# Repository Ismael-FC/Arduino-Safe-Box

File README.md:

# Arduino-Safe-Box

O projeto consiste num simples mecanismo de trancar e destrancar uma caixa, mediante a apresentação de password/PIN ou não. 

Materiais utilizados:
- Arduino MEGA;
- Breadboard;
- Sensor ultrassónico;
- Servomotor SG90;
- 2 LEDs;
- 3 Resistências de 220 Ohm;
- 1 Buzzer (passivo ou ativo);
- Display LED 16x2 I2C;
- Matriz de Botões 4x4;
- Sensor de vibração.

Modo de funcionamento:
Com PIN indefinido, a porta estará aberta e o utilizador terá a possibilidade de definir um PIN através da matriz de botões 
ao pressionar o botão A. Nesse caso, a máquina irá passar para um estado onde estará a guardar a password (limitada a 10 caracteres).
Se o utilizador se enganar, pode pressionar C; quando finalizar, deve pressionar #. O utilizador pode trancar a caixa com um botão externo. 

Definido um PIN, o sistema entra em stand-by. O sensor procura indivíduos próximos a cada 100 ms. Em caso de deteção, o display
irá saudar o indivíduo e apresentar as opções B para login e S para reset da password.

Se nas 3 tentativas de log-in o utilizador errar o PIN, o sistema entra em modo LOCK pelo que faz soar um alarme e impede novas tentativas de
log-in ou reset. Em caso de entrada forçada na caixa, um sensor de vibração será ativado o que também leva o sistema o modo LOCK.

Caso o utilizador acerte o PIN, o servmotor roda de modo a destrancar a caixa. O utilizador pode trancar a caixa com um botão externo. 
O sistema volta ao estado de stand-by.

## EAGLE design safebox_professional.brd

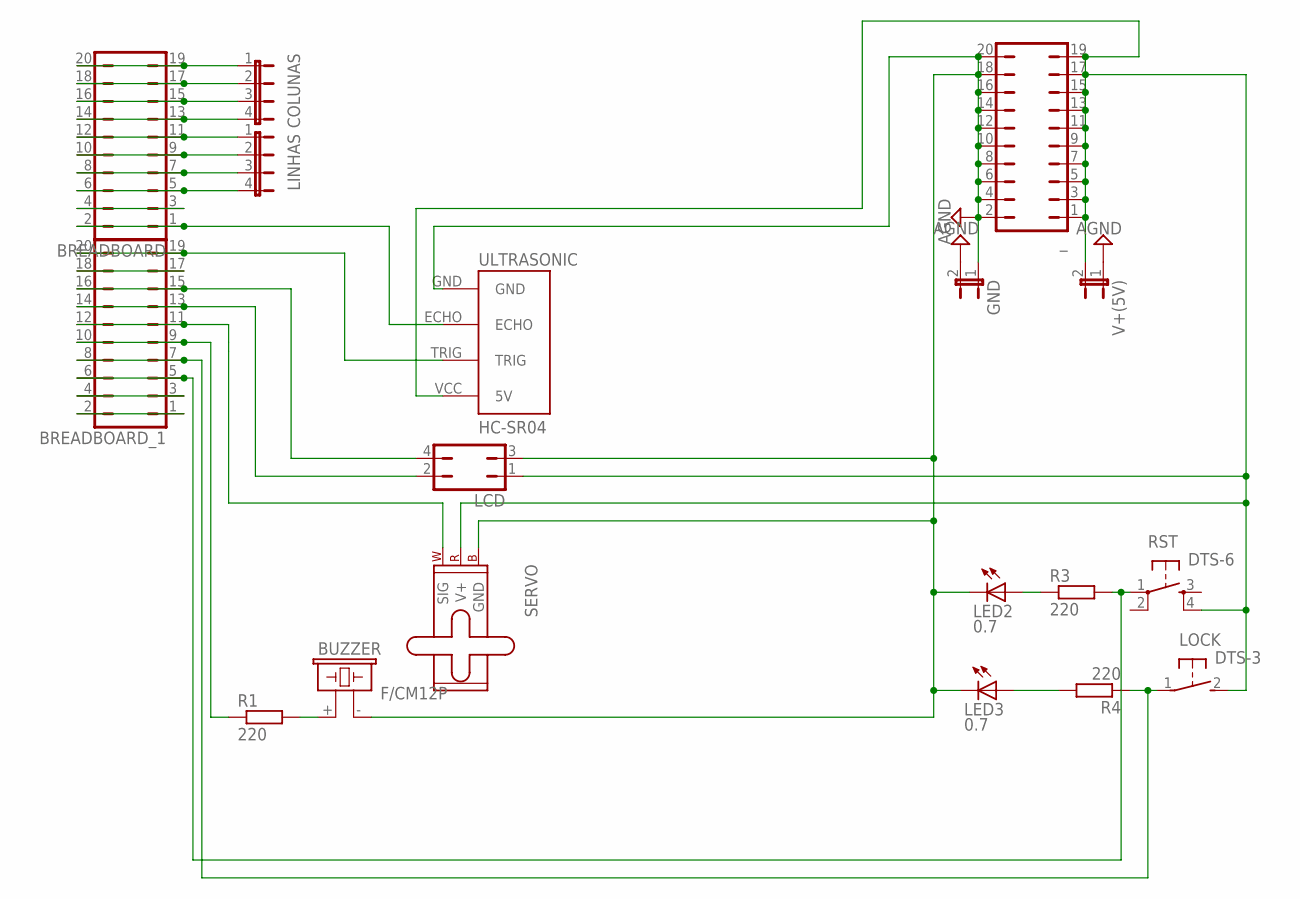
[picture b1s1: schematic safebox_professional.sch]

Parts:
BREADBOARD: JP10Q
BREADBOARD_1: JP10Q
BUZZER: F/CM12P
COLUNAS: JP4E; JP4
GND: JP1E; JP1
LCD: JP2Q
LED2, LED3: 0.7; LED5MM
LINHAS: JP4E; JP4
LOCK: DTS-3
M2: SERVO; 1X03
R1, R3, R4: 220; 0207/12
RST: DTS-6
ULTRASONIC: HC-SR04; HC-SR04_FOOTPRINT
V+(5V): JP1E; JP1
_: JP10Q

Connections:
AGND: BUZZER.- (2), GND.1, GND.2, LCD.3, LED2.K (C), LED3.K (C), M2.3 (GND), ULTRASONIC.GND, V+(5V).1, _.2, _.4, _.6, _.8, _.10, _.12, _.14, _.16, _.18, _.20
unnamed: BREADBOARD_1.5, BREADBOARD_1.6, R3.2, RST.1
unnamed: BREADBOARD_1.1, BREADBOARD_1.2
unnamed: BREADBOARD.19, BREADBOARD.20, COLUNAS.1
unnamed: BREADBOARD.17, BREADBOARD.18, COLUNAS.2
unnamed: BREADBOARD.15, BREADBOARD.16, COLUNAS.3
unnamed: BREADBOARD.13, BREADBOARD.14, COLUNAS.4
unnamed: BREADBOARD.11, BREADBOARD.12, LINHAS.1
unnamed: BREADBOARD.9, BREADBOARD.10, LINHAS.2
unnamed: BREADBOARD.7, BREADBOARD.8, LINHAS.3
unnamed: BREADBOARD.5, BREADBOARD.6, LINHAS.4
unnamed: LED2.A, R3.1
unnamed: BUZZER.+ (1), R1.2
unnamed: BREADBOARD.1, BREADBOARD.2, ULTRASONIC.ECHO
unnamed: BREADBOARD_1.15, BREADBOARD_1.16, LCD.4
unnamed: BREADBOARD_1.13, BREADBOARD_1.14, LCD.2
unnamed: BREADBOARD_1.17, BREADBOARD_1.18
unnamed: BREADBOARD_1.9, BREADBOARD_1.10, R1.1
unnamed: BREADBOARD_1.7, BREADBOARD_1.8, LOCK.1, R4.1
unnamed: BREADBOARD_1.11, BREADBOARD_1.12, M2.1 (SIG)
unnamed: BREADBOARD.3, BREADBOARD.4
unnamed: BREADBOARD_1.19, BREADBOARD_1.20, ULTRASONIC.TRIG
unnamed: BREADBOARD_1.3, BREADBOARD_1.4
unnamed: LED3.A, R4.2
unnamed: LCD.1, LOCK.2, M2.2 (V+), RST.4, ULTRASONIC.VCC (5V), V+(5V).2, _.1, _.3, _.5, _.7, _.9, _.11, _.13, _.15, _.17, _.19

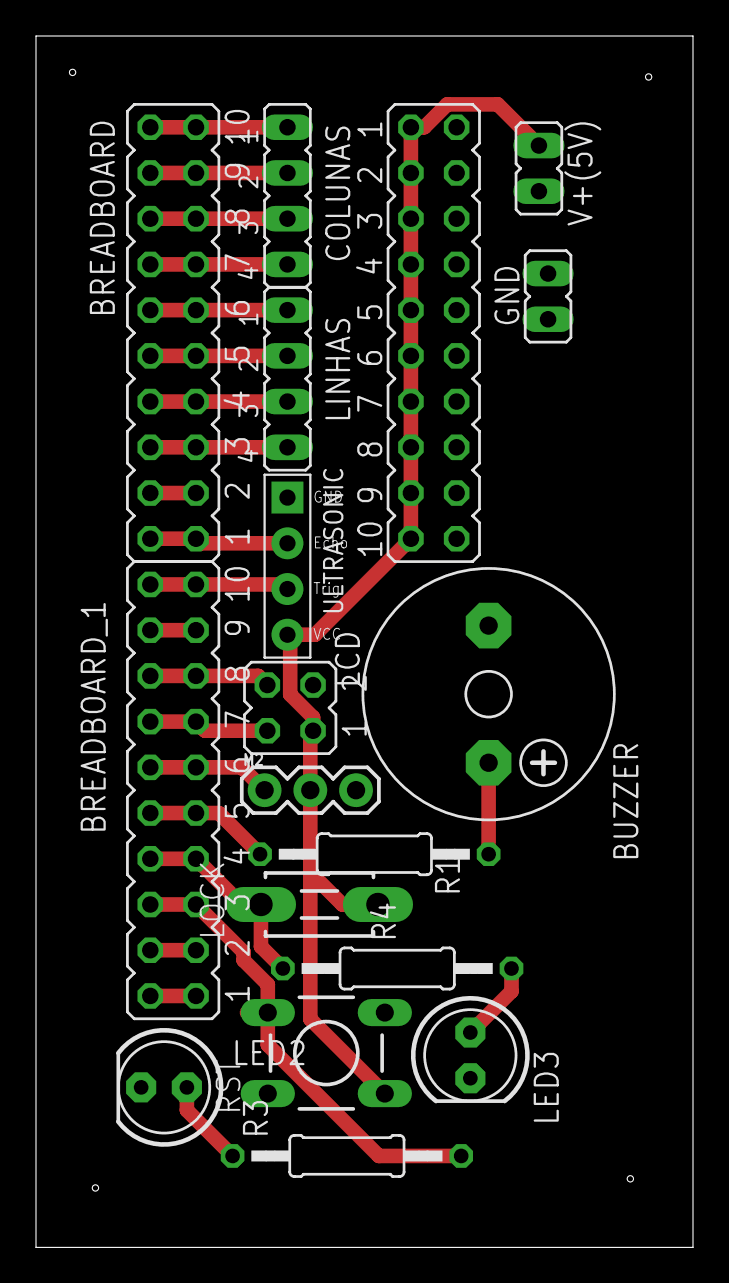
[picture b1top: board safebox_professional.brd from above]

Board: 2 copper layers, 36.5 x 67.3 mm, 18 parts (0 on the bottom side), 25 nets.

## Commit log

2025-02-09 Files

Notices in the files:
parts and their libraries:
SparkFun-Electromechanical: Licensing: Creative Commons ShareAlike 4.0 International - https://creativecommons.org/licenses/by-sa/4.0
